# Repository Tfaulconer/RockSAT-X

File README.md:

# RockSAT-X 2019

## Table of Contents
1. [Introduction](#intrduction)
2. [Design](#design)

### Introduction
The RockSat-X program provides customers a standardized, convenient way to deliver their payloads to a microgravity testing environment. The RockSat-X sounding rocket has an ejectable skin and nose cone that will expose customer payloads to the space environment fully at an apogee of 150-170 km. For more information please refer to the [RockSat-X 2019 Website](https://spacegrant.colorado.edu/national-programs/rs-x-home) 

The UNL RockSat-X payload experiment goal was to collect accelerometer, gyroscopic and GoPro data in a microgravity environment to help researchers at NASA Langley Research Center characterize, develop and streamline a mechanism for a deployable boom.

### Design
A full report can be see in the Final Report folder.

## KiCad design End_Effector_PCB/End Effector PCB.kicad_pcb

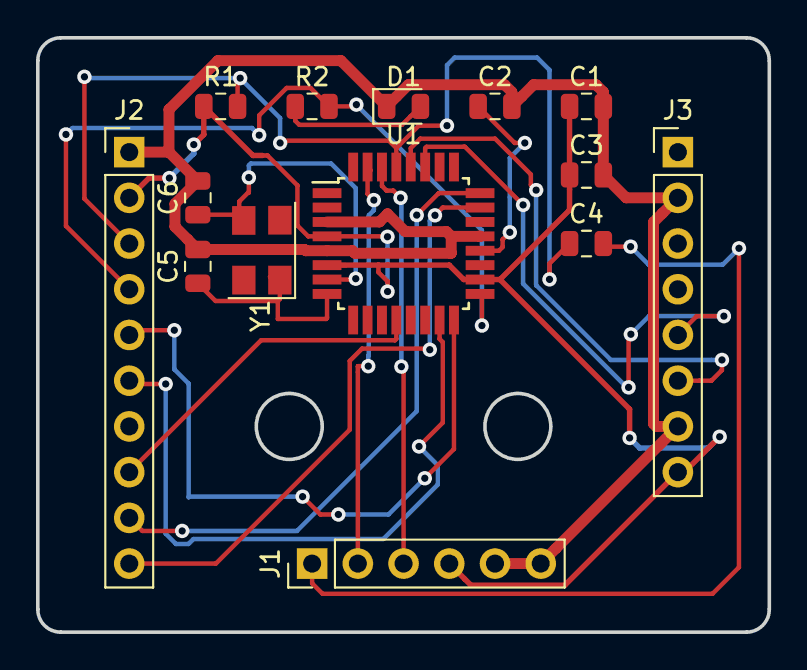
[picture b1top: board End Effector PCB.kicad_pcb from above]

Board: 2 copper layers, 40.6 x 33.0 mm, 14 parts (0 on the bottom side), 18 nets.

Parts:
C1, C2, C3, C4: 0.1u; C_0805_2012Metric
C5, C6: 22pF; C_0805_2012Metric
D1: LED; LED_0805_2012Metric
J1: Conn_01x06; PinHeader_1x06_P2.54mm_Vertical
J2: Conn_01x10; PinHeader_1x10_P2.54mm_Vertical
J3: Conn_01x08; PinHeader_1x08_P2.54mm_Vertical
R1: 10K; R_0805_2012Metric
R2: 1K; R_0805_2012Metric
U1: ATmega328P-AU; TQFP-32_7x7mm_P0.8mm
Y1: Crystal; Crystal_SMD_5032X-4Pin_5.0x3.2mm

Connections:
+5V: C1.1, C3.1, J1.4, J2.2, J3.8, R1.1, U1.4, U1.6, U1.18
ADC0: J2.10, U1.23
ADC1: J2.9, U1.24
GND: C1.2, C2.2, C3.2, C5.2, C6.2, D1.1, J1.5, J1.6, J2.1, J3.2, J3.7, U1.3, U1.5, U1.21
MISO: J2.5, U1.16
MOSI: J2.6, U1.15
unnamed: C2.1, U1.20
unnamed: C4.2, J1.1
unnamed: C5.1, U1.8, Y1.1
unnamed: C6.1, U1.7, Y1.2
unnamed: D1.2, R2.1
PB0: J2.8, U1.12
RESET: C4.1, J2.3, R1.2, U1.29
RXD: J1.3, U1.30
SCK: J2.4, R2.2, U1.17
SCL: J3.6, U1.28
SDA: J3.5, U1.27
TXD: J1.2, U1.31

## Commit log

2021-05-28 add end effector code and Main mission code
2021-05-28 add block diagrams, PCB files, and admin files
2021-05-28 added final report and user guide
2021-05-28 directory restructure
2021-05-28 deleting files due to file restructure
2021-05-28 updated readme and test
2021-05-28 better summary
2021-05-28 updated readme to add design heading
